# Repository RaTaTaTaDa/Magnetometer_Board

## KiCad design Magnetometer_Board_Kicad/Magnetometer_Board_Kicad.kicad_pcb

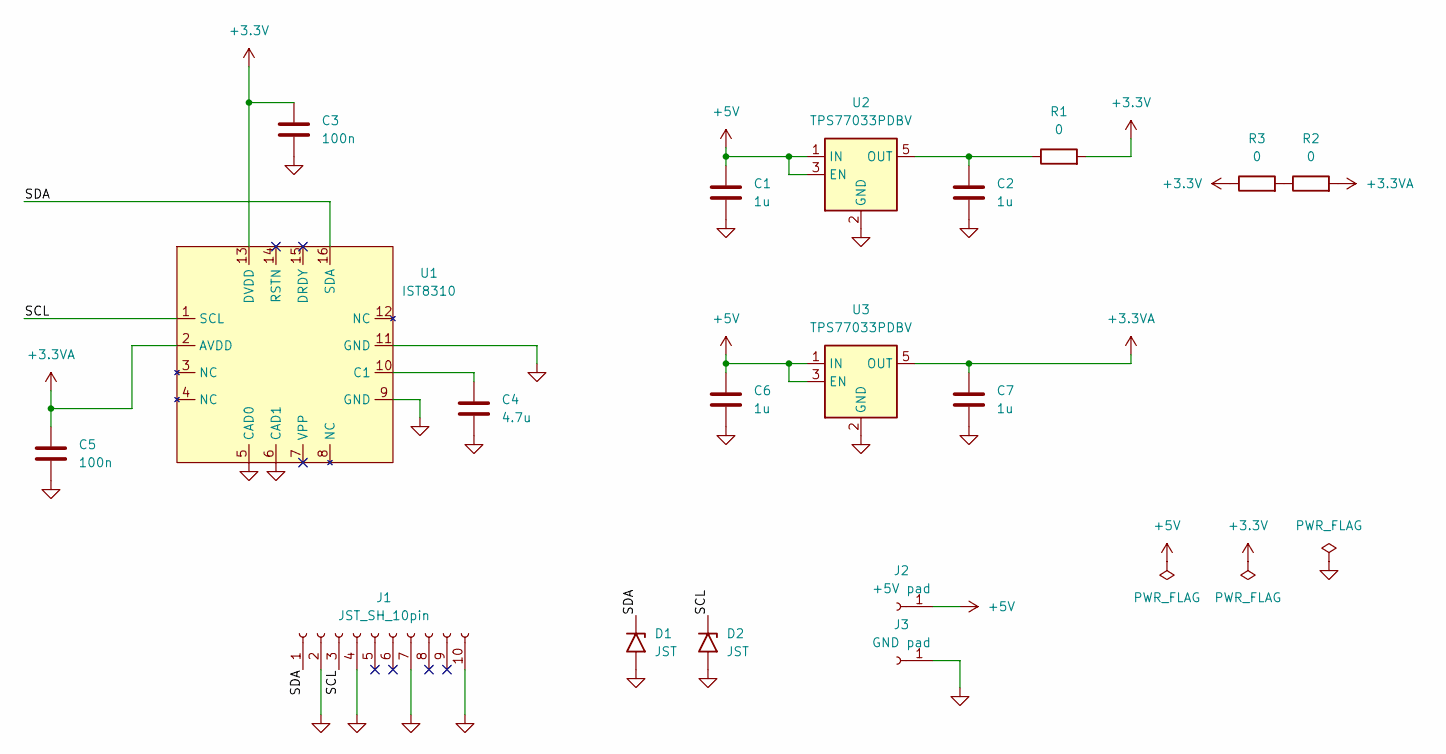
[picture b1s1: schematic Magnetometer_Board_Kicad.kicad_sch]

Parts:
C1, C2, C6, C7: 1u; C_0603_1608Metric; LCSC C77046
C3, C5: 100n; C_0603_1608Metric; LCSC C77055
C4: 4.7u; C_0603_1608Metric; LCSC C327022
D1, D2: JST; D_0402_1005Metric; LCSC C1869319
J1: JST_SH_10pin; JST_SHL_SM10B-SHLS-TF_1x10-1MP_P1.00mm_Horizontal; LCSC C160409
J2: +5V pad; SolderWirePad_1x01_SMD_3x6mm
J3: GND pad; SolderWirePad_1x01_SMD_3x6mm
R1, R2, R3: 0; R_0603_1608Metric; LCSC C95177
U1: IST8310; IST8310 LGA; Manufacturer Part Number IST8310; LCSC C2683055
U2, U3: TPS77033PDBV; SOT-23-5; LCSC C36996065

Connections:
+3.3V: C3.1, R1.2, R3.1, U1.13 (DVDD)
+3.3VA: C5.1, C7.1, R2.2, U1.2 (AVDD), U3.5 (OUT)
+5V: C1.1, C6.1, J2.1, U2.1 (IN), U2.3 (EN), U3.1 (IN), U3.3 (EN)
/SCL: D2.1 (A1), J1.3, U1.1 (SCL)
/SDA: D1.1 (A1), J1.1, U1.16 (SDA)
GND: C1.2, C2.2, C3.2, C4.2, C5.2, C6.2, C7.2, D1.2 (A2), D2.2 (A2), J1.2, J1.4, J1.7, J1.10, J3.1, U1.5 (CAD0), U1.6 (CAD1), U1.9 (GND), U1.11 (GND), U2.2 (GND), U2.4 (GND), U3.2 (GND), U3.4 (GND)
unnamed: R2.1, R3.2
unnamed: C4.1, U1.10 (C1)
unnamed: C2.1, R1.1, U2.5 (OUT)

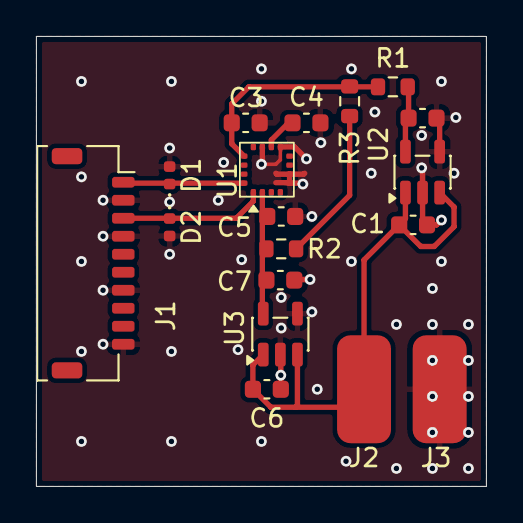
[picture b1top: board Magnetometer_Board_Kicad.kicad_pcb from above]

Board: 2 copper layers, 25.0 x 25.0 mm, 18 parts (0 on the bottom side), 9 nets.

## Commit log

2025-11-29 version 1.0 done
2025-11-30 production files done
